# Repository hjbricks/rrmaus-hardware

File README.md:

# rrmaus-hardware
Everything regarding the hardware of rrmaus

# V1-module-based

This is the original hardware based on moduled

# TODO: V2

All smd, but compatible with the V1 software

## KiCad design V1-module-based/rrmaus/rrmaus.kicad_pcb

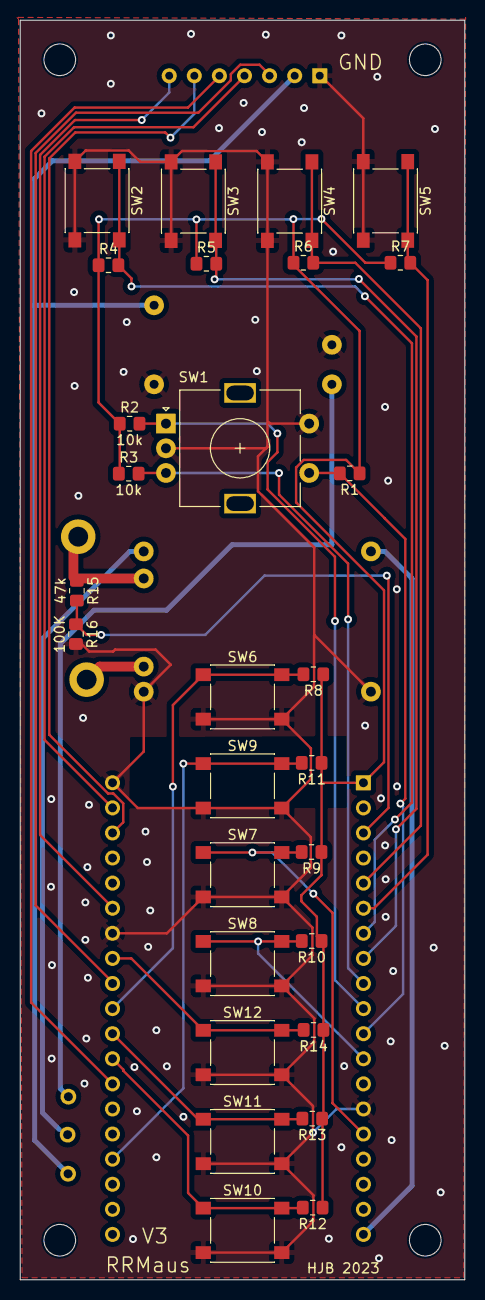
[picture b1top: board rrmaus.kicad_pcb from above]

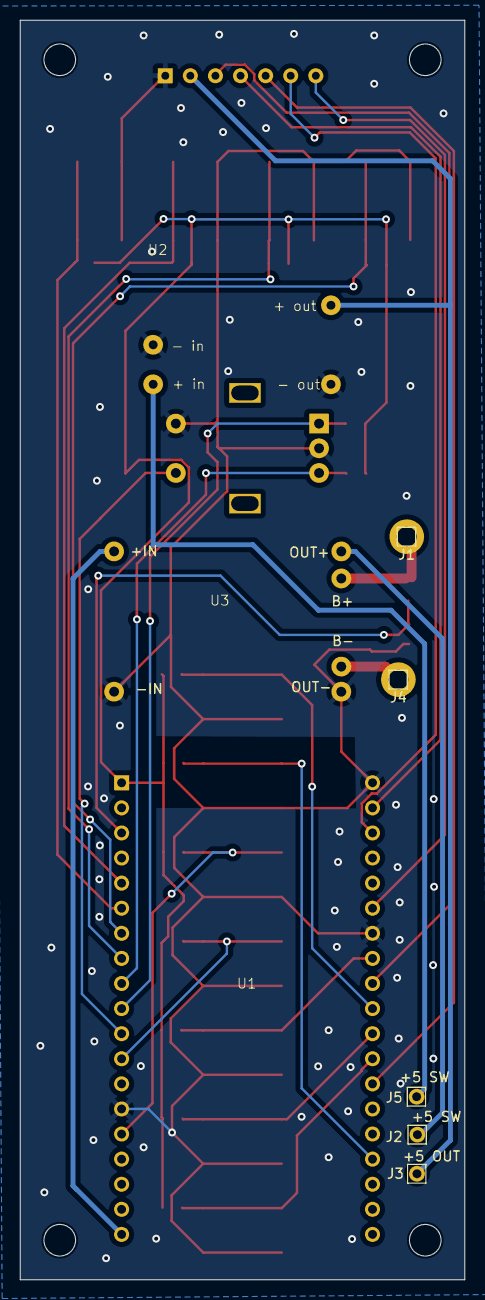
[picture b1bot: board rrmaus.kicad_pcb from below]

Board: 2 copper layers, 45.0 x 127.5 mm, 37 parts (8 on the bottom side), 28 nets.

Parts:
J1: VBAT+; Pin_D0.7mm_L6.5mm_W1.8mm_FlatFork
J2, J5: +5 SW; Pin_D0.7mm_L6.5mm_W1.8mm_FlatFork
J3: +5 OUT; Pin_D0.7mm_L6.5mm_W1.8mm_FlatFork
J4: VBAT-; Pin_D0.7mm_L6.5mm_W1.8mm_FlatFork
R1, R2, R3, R4, R5, R6, R7, R8, R9, R10, R11, R12, R13, R14: 10k; R_0805_2012Metric_Pad1.20x1.40mm_HandSolder
R15: 47k; R_0805_2012Metric_Pad1.20x1.40mm_HandSolder
R16: 100K; R_0805_2012Metric_Pad1.20x1.40mm_HandSolder
SW1: RotaryEncoder+Switch; RotaryEncoder_Alps_EC11E-Switch_Vertical_H20mm
SW2, SW3, SW4, SW5, SW6, SW7, SW8, SW9, SW10, SW11, SW12: SW_Push; SW_Push_1P1T_NO_6x6mm_H9.5mm
U1: ESP32 Wroom 38 pins; ESP32Wroom 38 pins
U2: STEPUP
U3: TP4056
U4: TFT_IPS_240x320

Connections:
+3.3V: R1.1, R2.1, R3.1, R4.1, R5.1, R6.1, R7.1, R8.1, R9.1, R10.1, R11.1, R12.1, R13.1, R14.1, U1.1 (3V3)
+5V: J2.1, U3.3 (OUT+)
GNDD: R16.2, SW1.C, SW1.S2, SW2.2, SW3.2, SW4.2, SW5.2, SW6.2, SW7.2, SW8.2, SW9.2, SW10.2, SW11.2, SW12.2, U1.14 (GND), U1.32 (GND), U1.38 (GND), U2.2 (-IN), U2.3 (-OUT), U3.1 (-IN), U3.6 (OUT-), U4.1 (GND)
unnamed: J3.1, U2.4 (+OUT), U4.2 (VCC)
unnamed: J4.1, U3.5 (B-)
unnamed: J5.1, U2.1 (+IN)
unnamed: U1.19 (5V), U3.2 (+IN)
unnamed: U1.26 (GPIO4), U4.5 (RST)
unnamed: R8.2, SW6.1, U1.29 (GPIO5)
unnamed: R9.2, SW7.1, U1.15 (GPIO13)
unnamed: R10.2, SW8.1, U1.12 (GPIO14)
unnamed: R11.2, SW9.1, U1.23 (GPIO15)
unnamed: R12.2, SW10.1, U1.27 (GPIO16)
unnamed: R13.2, SW11.1, U1.28 (GPIO17)
unnamed: U1.30 (GPIO18), U4.3 (SCLK)
unnamed: R14.2, SW12.1, U1.31 (GPIO19)
unnamed: U1.33 (GPIO21), U4.7 (CS)
unnamed: U1.36 (GPIO22), U4.6 (DC)
unnamed: U1.37 (GPIO23), U4.4 (MOSI)
unnamed: R3.2, SW1.B, U1.9 (GPIO25)
unnamed: R2.2, SW1.A, U1.10 (GPIO26)
unnamed: R1.2, SW1.S1, U1.11 (GPIO27)
unnamed: R4.2, SW2.1, U1.7 (GPIO32)
unnamed: R5.2, SW3.1, U1.8 (GPIO33)
unnamed: R6.2, SW4.1, U1.5 (GPIO34)
unnamed: R7.2, SW5.1, U1.6 (GPIO35)
unnamed: R15.2, R16.1, U1.3 (VP)
VDD: J1.1, R15.1, U3.4 (B+)

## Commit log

2024-06-04 Added V1 module based hardware
2024-06-04 Going to start with the V2 hardware
2024-06-04 Made a copy of V1 as a start of V2, leave V1 for now
